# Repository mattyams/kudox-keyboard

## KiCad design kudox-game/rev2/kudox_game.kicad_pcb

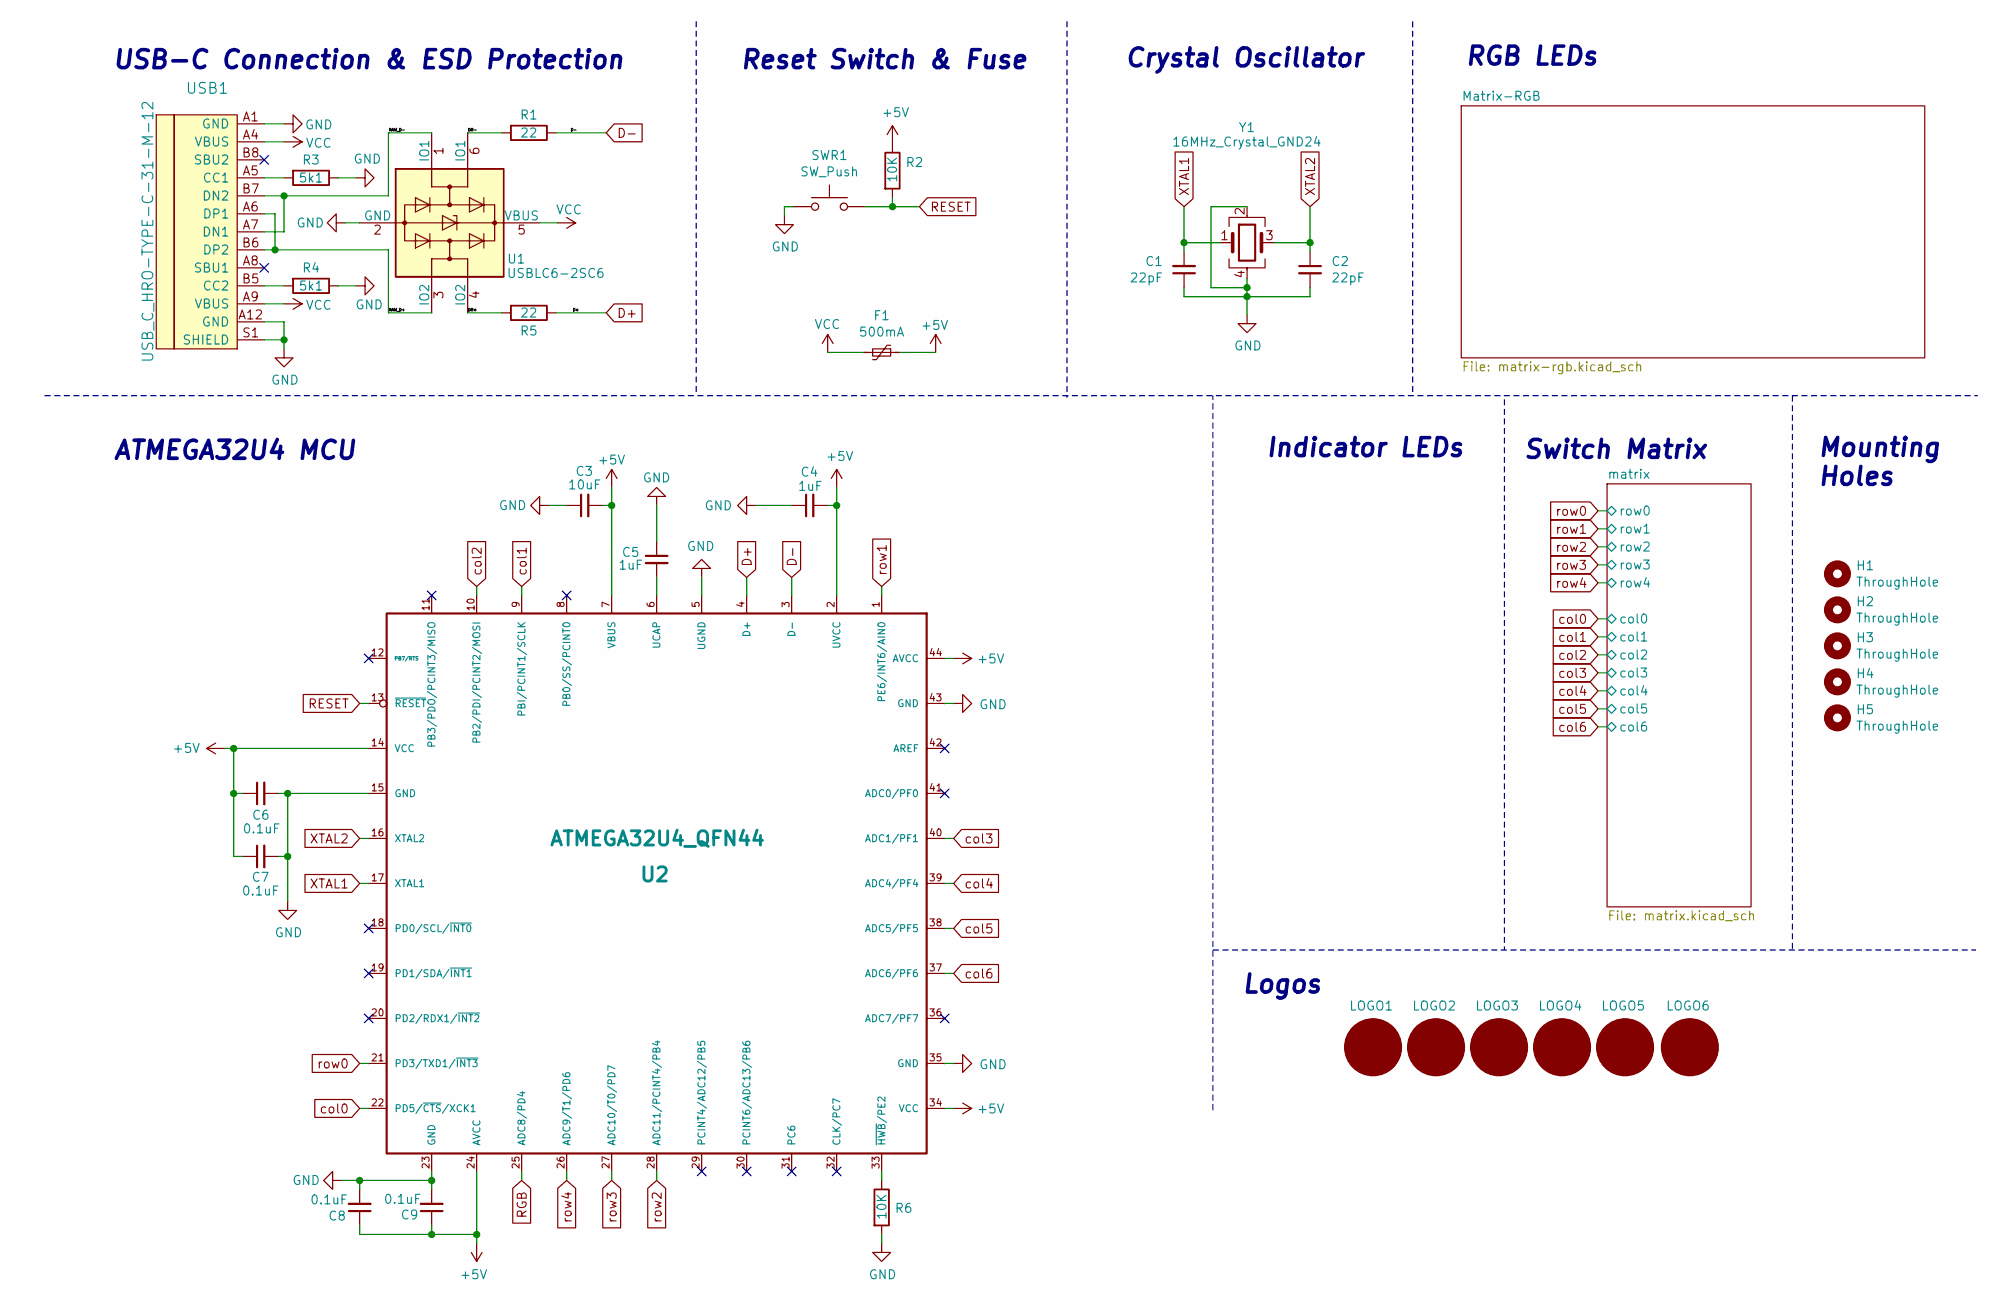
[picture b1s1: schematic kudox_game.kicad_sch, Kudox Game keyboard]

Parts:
C1, C2: 22pF; C_0805_2012Metric_Pad1.18x1.45mm_HandSolder; LCSC C1804
C3: 10uF; C_0805_2012Metric_Pad1.18x1.45mm_HandSolder; LCSC C15850
C4, C5: 1uF; C_0805_2012Metric_Pad1.18x1.45mm_HandSolder; LCSC C28323
C6, C7, C8, C9: 0.1uF; C_0805_2012Metric_Pad1.18x1.45mm_HandSolder; LCSC C28233
F1: 500mA; Fuse_1206_3216Metric_Pad1.42x1.75mm_HandSolder; LCSC C70068
H1, H2, H3, H4, H5: ThroughHole; HOLE_M3
LOGO1, LOGO2: arisutea_logo; warning_sign_3.6x3.2mm
LOGO3, LOGO4: OSHW Logo; osh-logo
LOGO5, LOGO6: QMK_Logo_Light
R1, R5: 22; R_0805_2012Metric_Pad1.20x1.40mm_HandSolder; LCSC C17561
R2, R6: 10K; R_0805_2012Metric_Pad1.20x1.40mm_HandSolder; LCSC C17414
R3, R4: 5k1; R_0805_2012Metric_Pad1.20x1.40mm_HandSolder; LCSC C27834
SWR1: SW_Push; SW_SPST_TL3342; LCSC C318884
U1: USBLC6-2SC6; SOT-23-6_Handsoldering; LCSC C7519
U2: ATMEGA32U4_QFN44; TQFP-44_10x10mm_P0.8mm; LCSC C44854
USB1: USB_C_HRO-TYPE-C-31-M-12; USB_C-31-M-12; LCSC C319148
Y1: 16MHz_Crystal_GND24; Crystal_SMD_TXC_7M-4Pin_3.2x2.5mm_HandSoldering; LCSC C89371

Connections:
+5V: C3.2, C4.2, C6.1, C7.1, C8.1, C9.1, F1.1, R2.1, U2.2 (UVCC), U2.7 (VBUS), U2.14 (VCC), U2.24 (AVCC), U2.34 (VCC), U2.44 (AVCC); also elsewhere on the board
/DR+: R5.2, U1.4 (IO2)
/DR-: R1.2, U1.6 (IO1)
/RAW_D+: U1.3 (IO2), USB1.A6 (DP1), USB1.B6 (DP2)
/RAW_D-: U1.1 (IO1), USB1.A7 (DN1), USB1.B7 (DN2)
D+: R5.1, U2.4 (D+)
D-: R1.1, U2.3 (D-)
GND: C1.1, C2.2, C3.1, C4.1, C5.1, C6.2, C7.2, C8.2, C9.2, R3.1, R4.1, R6.2, SWR1.1, U1.2 (GND), U2.5 (UGND), U2.15 (GND), U2.23 (GND), U2.35 (GND), U2.43 (GND), USB1.A1 (GND), USB1.A12 (GND), USB1.S1 (SHIELD), Y1.2, Y1.4; also elsewhere on the board
unnamed: C5.2, U2.6 (UCAP)
unnamed: R3.2, USB1.A5 (CC1)
unnamed: R4.2, USB1.B5 (CC2)
unnamed: R6.1, U2.33 (~HWB/PE2)
RESET: R2.2, SWR1.2, U2.13 (~RESET)
RGB: U2.25 (ADC8/PD4); also elsewhere on the board
VCC: F1.2, U1.5 (VBUS), USB1.A4 (VBUS), USB1.A9 (VBUS)
XTAL1: C1.2, U2.17 (XTAL1), Y1.1
XTAL2: C2.1, U2.16 (XTAL2), Y1.3
col0: U2.22 (PD5/~CTS/XCK1); also elsewhere on the board
col1: U2.9 (PBI/PCINT1/SCLK); also elsewhere on the board
col2: U2.10 (PB2/PDI/PCINT2/MOSI); also elsewhere on the board
col3: U2.40 (ADC1/PF1); also elsewhere on the board
col4: U2.39 (ADC4/PF4); also elsewhere on the board
col5: U2.38 (ADC5/PF5); also elsewhere on the board
col6: U2.37 (ADC6/PF6); also elsewhere on the board
row0: U2.21 (PD3/TXD1/~INT3); also elsewhere on the board
row1: U2.1 (PE6/INT6/AIN0); also elsewhere on the board
row2: U2.28 (ADC11/PCINT4/PB4); also elsewhere on the board
row3: U2.27 (ADC10/T0/PD7); also elsewhere on the board
row4: U2.26 (ADC9/T1/PD6); also elsewhere on the board

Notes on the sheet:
Indicator LEDs
ATMEGA32U4 MCU
USB-C Connection & ESD Protection
Logos
Mounting Holes
Reset Switch & Fuse
Switch Matrix
RGB LEDs
Crystal Oscillator

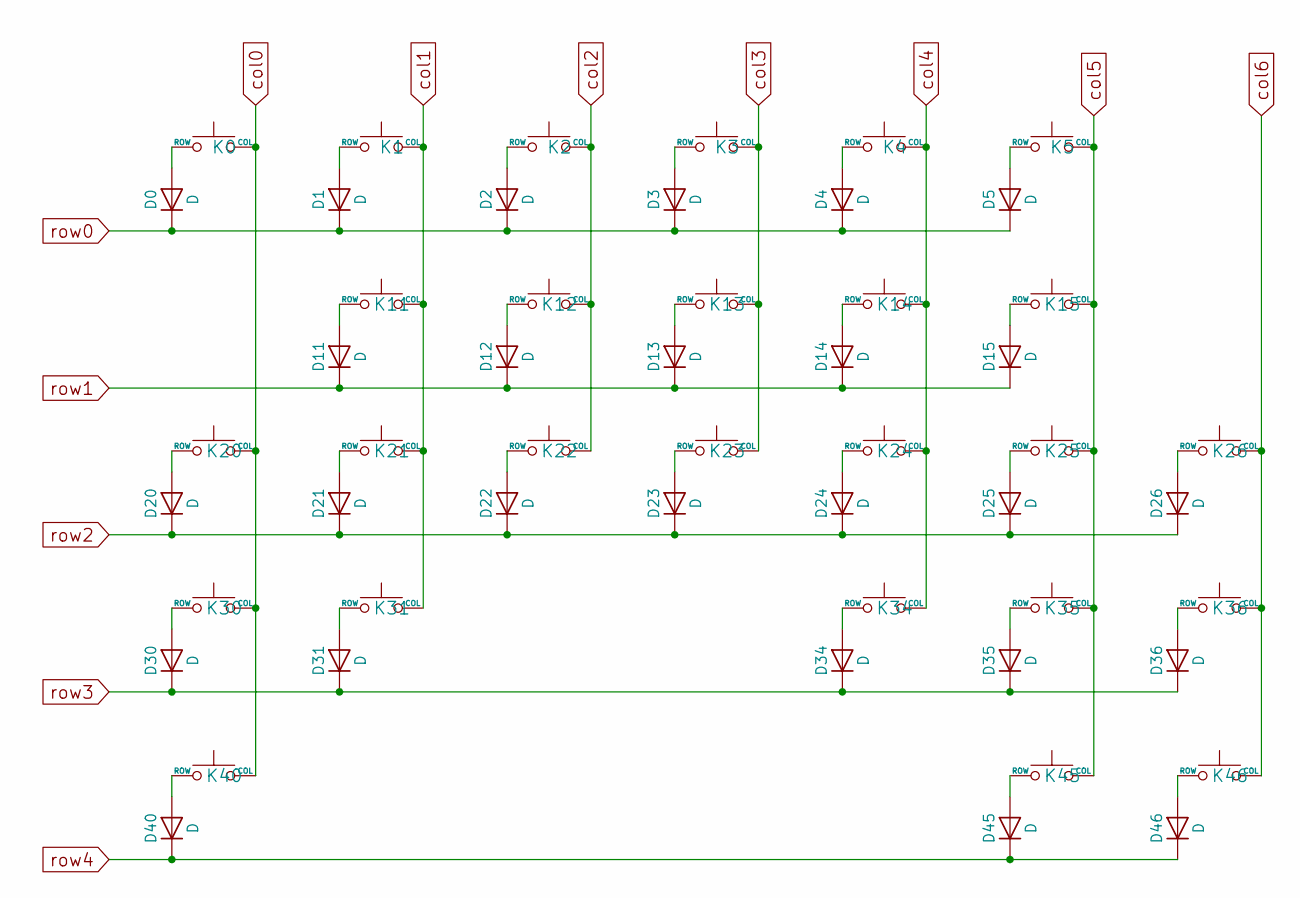
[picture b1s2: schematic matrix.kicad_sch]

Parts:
D0, D1, D2, D3, D4, D5, D11, D12, D13, D14, D15, D20, D21, D22, D23, D24, D25, D26, D30, D31, D34, D35, D36, D40, D45, D46: D; D_THT_7.62_SOD-123_Single_Side
K0, K1, K2, K3, K4, K5, K11, K12, K13, K14, K15, K20, K21, K22, K23, K24, K25, K26, K31, K34, K35, K36: KEYSW; SW_Hotswap_Kailh_1.00u
K30, K40, K45: KEYSW; SW_Hotswap_Kailh_1.50u
K46: KEYSW; SW_Hotswap_Kailh_2.00u

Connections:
unnamed: D0.2 (A), K0.2 (ROW)
unnamed: D1.2 (A), K1.2 (ROW)
unnamed: D2.2 (A), K2.2 (ROW)
unnamed: D3.2 (A), K3.2 (ROW)
unnamed: D4.2 (A), K4.2 (ROW)
unnamed: D5.2 (A), K5.2 (ROW)
unnamed: D11.2 (A), K11.2 (ROW)
unnamed: D12.2 (A), K12.2 (ROW)
unnamed: D13.2 (A), K13.2 (ROW)
unnamed: D14.2 (A), K14.2 (ROW)
unnamed: D15.2 (A), K15.2 (ROW)
unnamed: D20.2 (A), K20.2 (ROW)
unnamed: D21.2 (A), K21.2 (ROW)
unnamed: D22.2 (A), K22.2 (ROW)
unnamed: D23.2 (A), K23.2 (ROW)
unnamed: D24.2 (A), K24.2 (ROW)
unnamed: D25.2 (A), K25.2 (ROW)
unnamed: D26.2 (A), K26.2 (ROW)
unnamed: D30.2 (A), K30.2 (ROW)
unnamed: D31.2 (A), K31.2 (ROW)
unnamed: D34.2 (A), K34.2 (ROW)
unnamed: D35.2 (A), K35.2 (ROW)
unnamed: D36.2 (A), K36.2 (ROW)
unnamed: D40.2 (A), K40.2 (ROW)
unnamed: D45.2 (A), K45.2 (ROW)
unnamed: D46.2 (A), K46.2 (ROW)
col0: K0.1 (COL), K20.1 (COL), K30.1 (COL), K40.1 (COL); also elsewhere on the board
col1: K1.1 (COL), K11.1 (COL), K21.1 (COL), K31.1 (COL); also elsewhere on the board
col2: K2.1 (COL), K12.1 (COL), K22.1 (COL); also elsewhere on the board
col3: K3.1 (COL), K13.1 (COL), K23.1 (COL); also elsewhere on the board
col4: K4.1 (COL), K14.1 (COL), K24.1 (COL), K34.1 (COL); also elsewhere on the board
col5: K5.1 (COL), K15.1 (COL), K25.1 (COL), K35.1 (COL), K45.1 (COL); also elsewhere on the board
col6: K26.1 (COL), K36.1 (COL), K46.1 (COL); also elsewhere on the board
row0: D0.1 (K), D1.1 (K), D2.1 (K), D3.1 (K), D4.1 (K), D5.1 (K); also elsewhere on the board
row1: D11.1 (K), D12.1 (K), D13.1 (K), D14.1 (K), D15.1 (K); also elsewhere on the board
row2: D20.1 (K), D21.1 (K), D22.1 (K), D23.1 (K), D24.1 (K), D25.1 (K), D26.1 (K); also elsewhere on the board
row3: D30.1 (K), D31.1 (K), D34.1 (K), D35.1 (K), D36.1 (K); also elsewhere on the board
row4: D40.1 (K), D45.1 (K), D46.1 (K); also elsewhere on the board

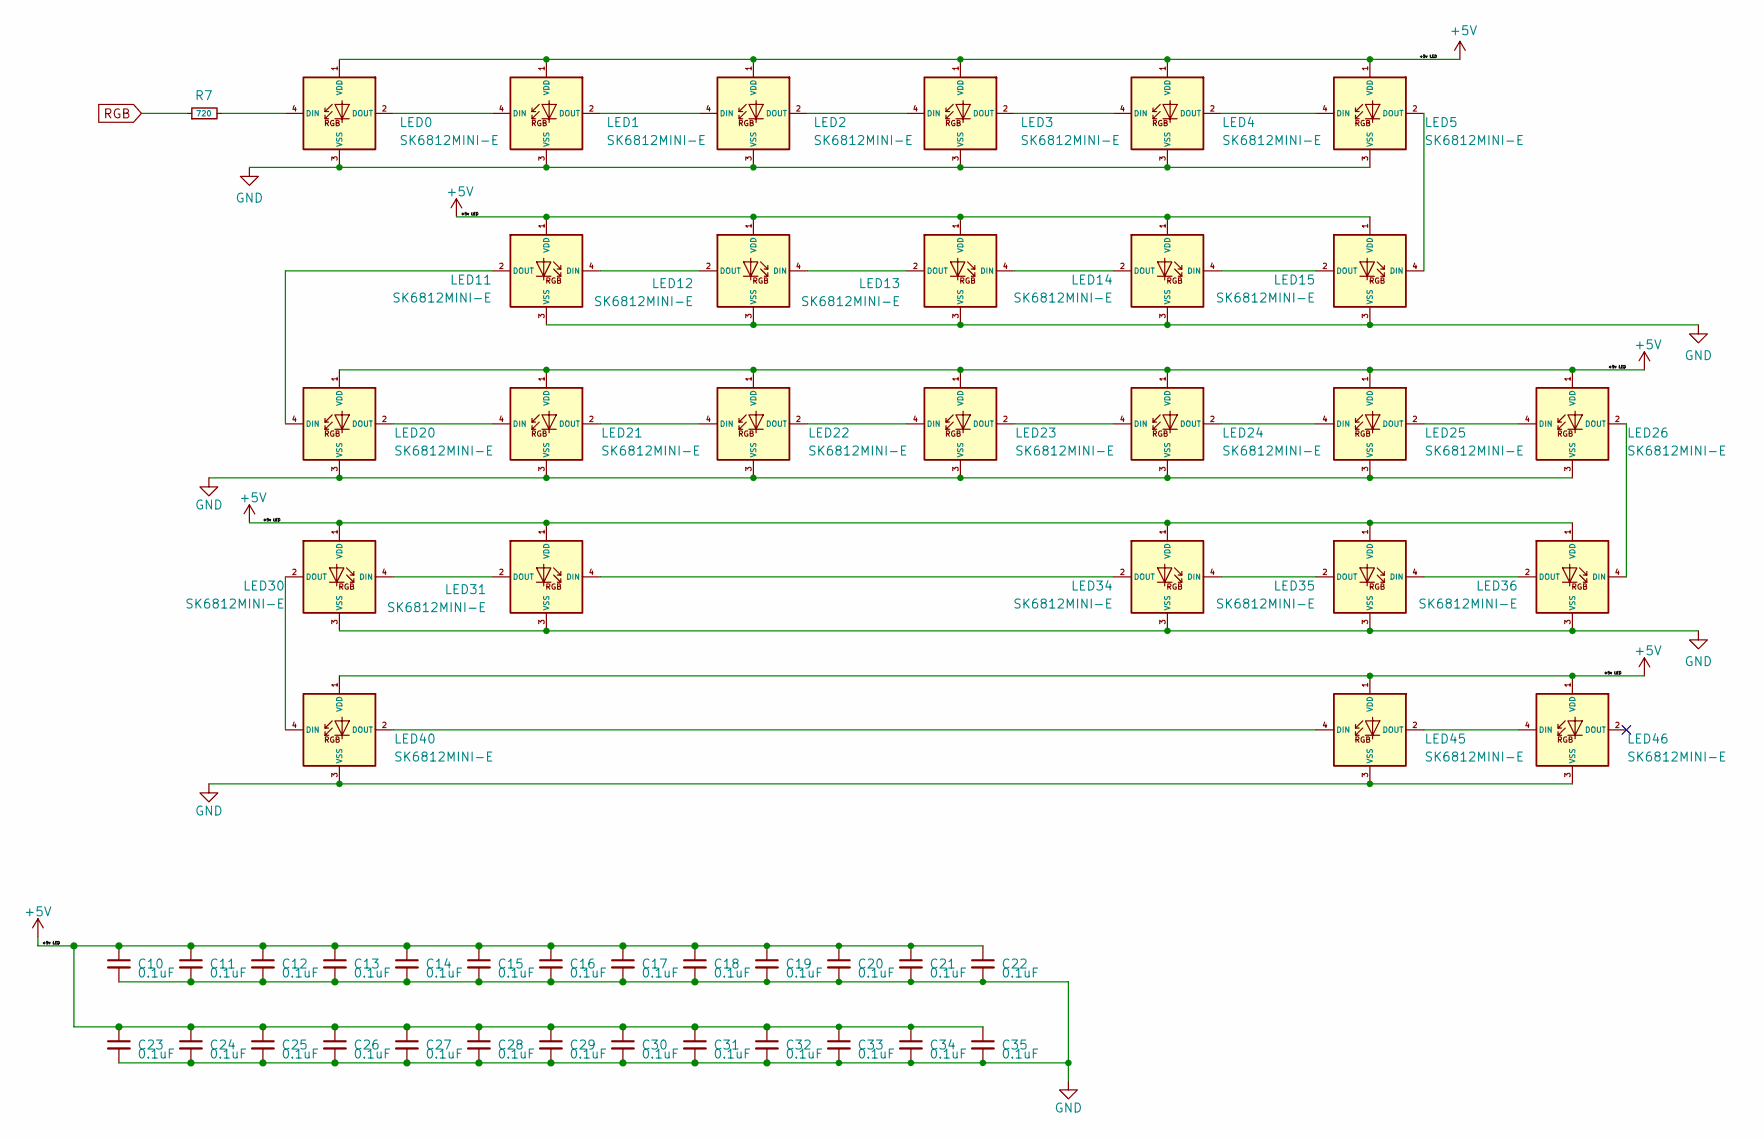
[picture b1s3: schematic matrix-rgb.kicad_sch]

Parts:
C10, C11, C12, C13, C14, C15, C16, C17, C18, C19, C20, C21, C22, C23, C24, C25, C26, C27, C28, C29, C30, C31, C32, C33, C34, C35: 0.1uF; C_0603_1608Metric_Pad1.08x0.95mm_HandSolder; LCSC C28233
LED0, LED1, LED2, LED3, LED4, LED5, LED20, LED21, LED22, LED23, LED24, LED25, LED26, LED40, LED45, LED46: SK6812MINI-E; LED_MX_SK6812MINI-E
LED11, LED12, LED13, LED14, LED15, LED30, LED31, LED34, LED35, LED36: SK6812MINI-E; LED_MX_SK6812MINI-E_REV
R7: 720; R_0805_2012Metric_Pad1.20x1.40mm_HandSolder; LCSC C17818

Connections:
+5V: C10.1, C11.1, C12.1, C13.1, C14.1, C15.1, C16.1, C17.1, C18.1, C19.1, C20.1, C21.1, C22.1, C23.1, C24.1, C25.1, C26.1, C27.1, C28.1, C29.1, C30.1, C31.1, C32.1, C33.1, C34.1, C35.1, LED0.1 (VDD), LED1.1 (VDD), LED2.1 (VDD), LED3.1 (VDD), LED4.1 (VDD), LED5.1 (VDD), LED11.1 (VDD), LED12.1 (VDD), LED13.1 (VDD), LED14.1 (VDD), LED15.1 (VDD), LED20.1 (VDD), LED21.1 (VDD), LED22.1 (VDD), LED23.1 (VDD), LED24.1 (VDD), LED25.1 (VDD), LED26.1 (VDD), LED30.1 (VDD), LED31.1 (VDD), LED34.1 (VDD), LED35.1 (VDD), LED36.1 (VDD), LED40.1 (VDD), LED45.1 (VDD), LED46.1 (VDD); also elsewhere on the board
GND: C10.2, C11.2, C12.2, C13.2, C14.2, C15.2, C16.2, C17.2, C18.2, C19.2, C20.2, C21.2, C22.2, C23.2, C24.2, C25.2, C26.2, C27.2, C28.2, C29.2, C30.2, C31.2, C32.2, C33.2, C34.2, C35.2, LED0.3 (VSS), LED1.3 (VSS), LED2.3 (VSS), LED3.3 (VSS), LED4.3 (VSS), LED5.3 (VSS), LED11.3 (VSS), LED12.3 (VSS), LED13.3 (VSS), LED14.3 (VSS), LED15.3 (VSS), LED20.3 (VSS), LED21.3 (VSS), LED22.3 (VSS), LED23.3 (VSS), LED24.3 (VSS), LED25.3 (VSS), LED26.3 (VSS), LED30.3 (VSS), LED31.3 (VSS), LED34.3 (VSS), LED35.3 (VSS), LED36.3 (VSS), LED40.3 (VSS), LED45.3 (VSS), LED46.3 (VSS); also elsewhere on the board
unnamed: LED1.2 (DOUT), LED2.4 (DIN)
unnamed: LED0.2 (DOUT), LED1.4 (DIN)
unnamed: LED2.2 (DOUT), LED3.4 (DIN)
unnamed: LED3.2 (DOUT), LED4.4 (DIN)
unnamed: LED4.2 (DOUT), LED5.4 (DIN)
unnamed: LED5.2 (DOUT), LED15.4 (DIN)
unnamed: LED11.2 (DOUT), LED20.4 (DIN)
unnamed: LED11.4 (DIN), LED12.2 (DOUT)
unnamed: LED12.4 (DIN), LED13.2 (DOUT)
unnamed: LED13.4 (DIN), LED14.2 (DOUT)
unnamed: LED14.4 (DIN), LED15.2 (DOUT)
unnamed: LED20.2 (DOUT), LED21.4 (DIN)
unnamed: LED21.2 (DOUT), LED22.4 (DIN)
unnamed: LED22.2 (DOUT), LED23.4 (DIN)
unnamed: LED23.2 (DOUT), LED24.4 (DIN)
unnamed: LED24.2 (DOUT), LED25.4 (DIN)
unnamed: LED25.2 (DOUT), LED26.4 (DIN)
unnamed: LED26.2 (DOUT), LED36.4 (DIN)
unnamed: LED30.2 (DOUT), LED40.4 (DIN)
unnamed: LED30.4 (DIN), LED31.2 (DOUT)
unnamed: LED31.4 (DIN), LED34.2 (DOUT)
unnamed: LED34.4 (DIN), LED35.2 (DOUT)
unnamed: LED35.4 (DIN), LED36.2 (DOUT)
unnamed: LED40.2 (DOUT), LED45.4 (DIN)
unnamed: LED45.2 (DOUT), LED46.4 (DIN)
unnamed: LED0.4 (DIN), R7.2
RGB: R7.1; also elsewhere on the board

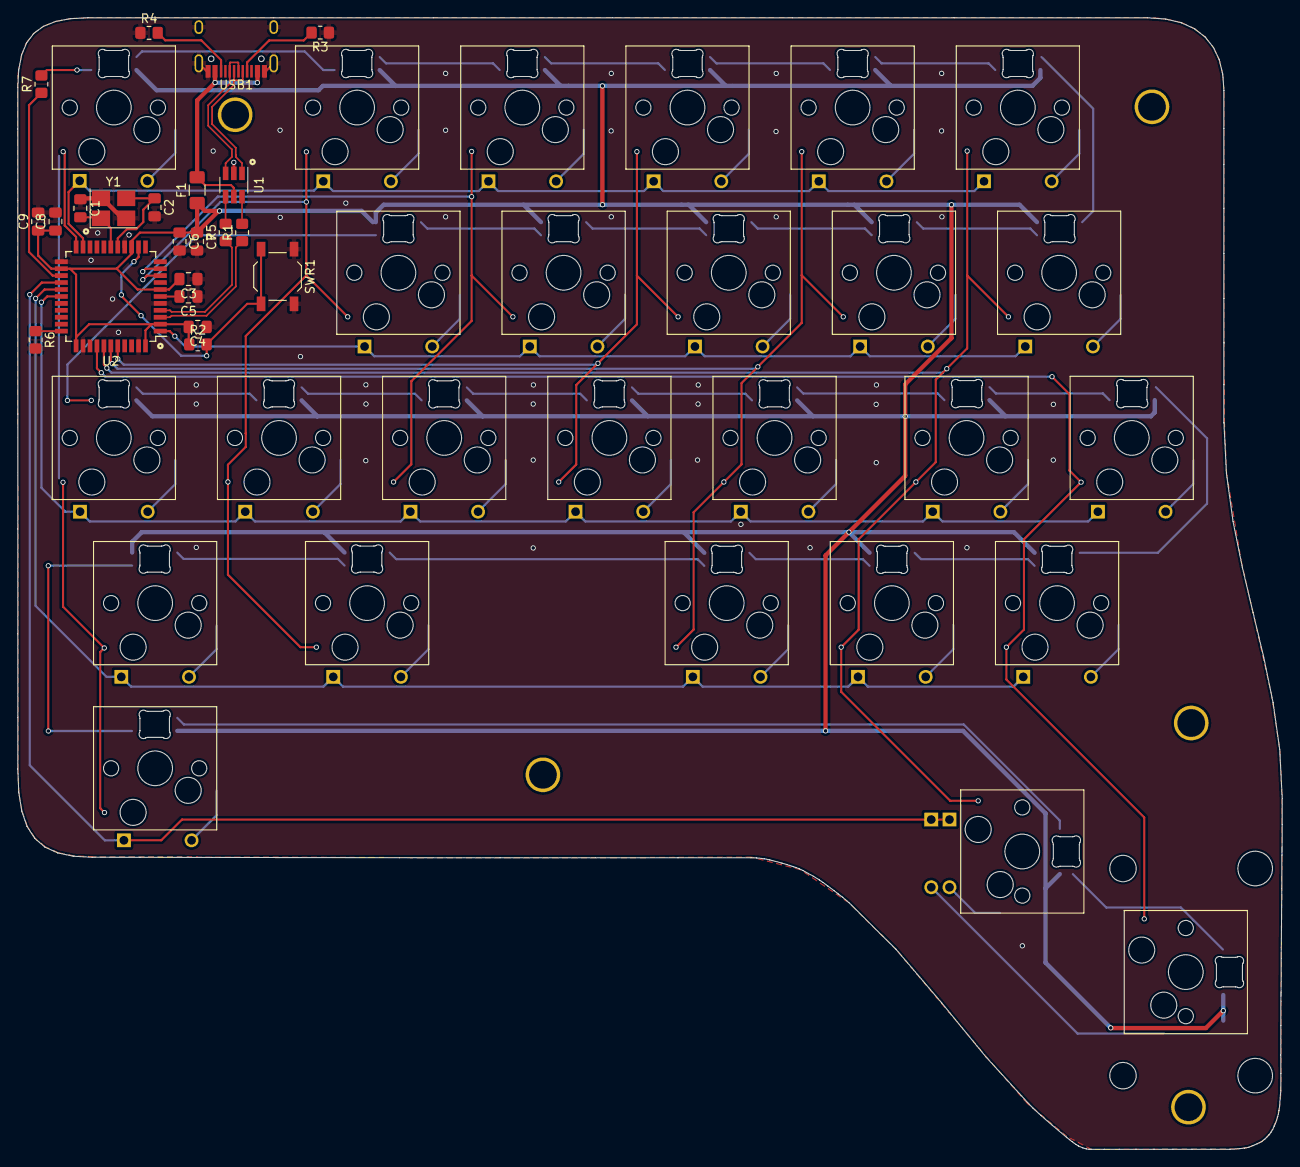
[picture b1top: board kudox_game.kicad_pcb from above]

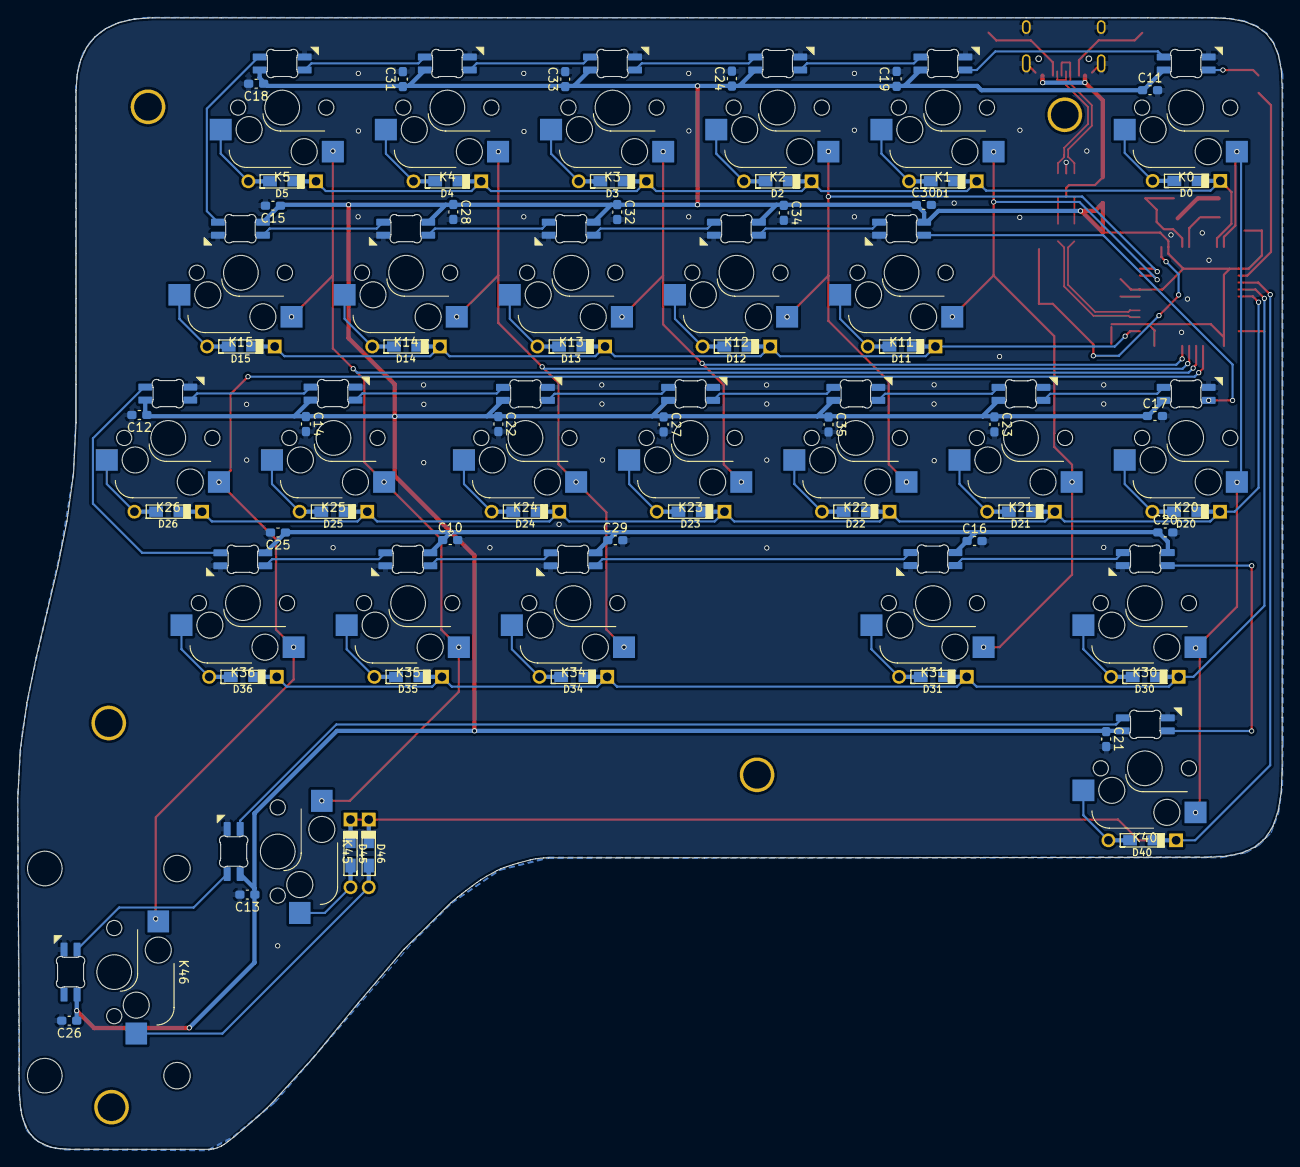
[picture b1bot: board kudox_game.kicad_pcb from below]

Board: 2 copper layers, 145.7 x 130.4 mm, 137 parts (52 on the bottom side), 81 nets.

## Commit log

2021-12-20 rgb stuff
